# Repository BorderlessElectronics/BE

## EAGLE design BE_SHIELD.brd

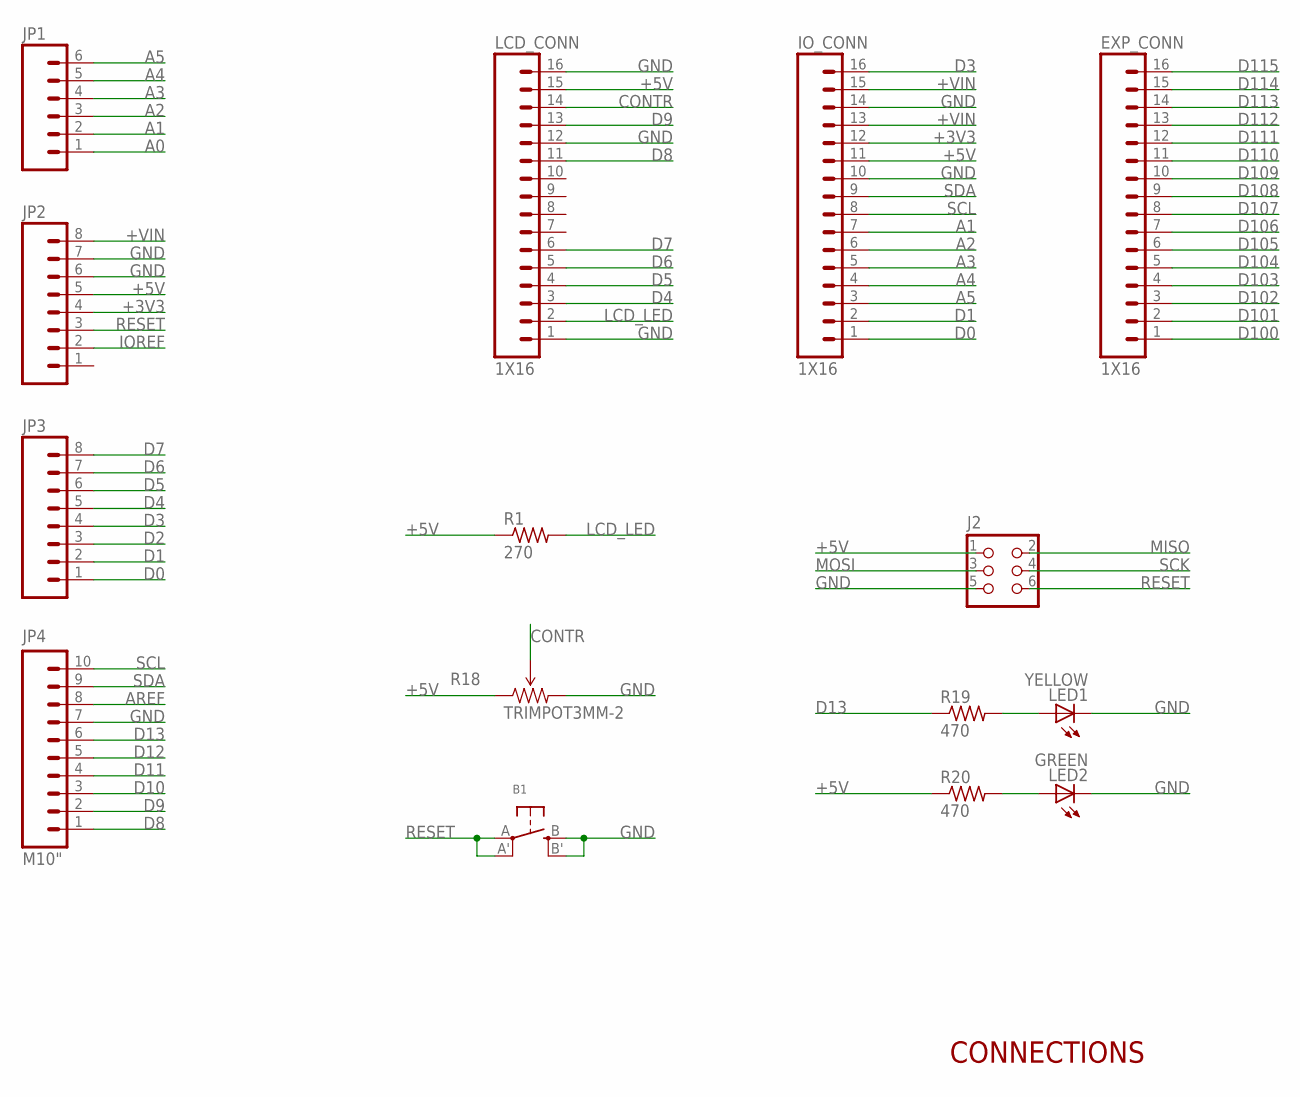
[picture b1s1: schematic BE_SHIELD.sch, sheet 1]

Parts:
B1: SWITCH_TACT_SMT; EVQ-Q2
EXP_CONN: 1X16; 1X16_SMD
IO_CONN: 1X16; 1X16_SMD
J2: CON_HEADER_2X03-SMD; M2X3_SMD
JP1: M06SIP; 1X06
JP2, JP3: M081X08; 1X08
JP4: M10"; 1X10
LCD_CONN: 1X16; 1X16_SMD
LED1: YELLOW; CHIP-LED0805
LED2: GREEN; CHIP-LED0805
R1: 270; R0603
R18: TRIMPOT3MM-2; TRIMPOT-3MM-2
R19, R20: 470; R0603

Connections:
+3V3: IO_CONN.12, JP2.4; also elsewhere on the board
+5V: IO_CONN.11, J2.1, JP2.5, LCD_CONN.15, R1.1, R18.1 (CCW), R20.1; also elsewhere on the board
+VIN: IO_CONN.13, IO_CONN.15, JP2.8; also elsewhere on the board
A0: JP1.1; also elsewhere on the board
A1: IO_CONN.7, JP1.2; also elsewhere on the board
A2: IO_CONN.6, JP1.3; also elsewhere on the board
A3: IO_CONN.5, JP1.4; also elsewhere on the board
A4: IO_CONN.4, JP1.5; also elsewhere on the board
A5: IO_CONN.3, JP1.6; also elsewhere on the board
AREF: JP4.8
CONTR: LCD_CONN.14, R18.2 (WIPER); also elsewhere on the board
D0: IO_CONN.1, JP3.1; also elsewhere on the board
D1: IO_CONN.2, JP3.2; also elsewhere on the board
D2: JP3.3; also elsewhere on the board
D3: IO_CONN.16, JP3.4; also elsewhere on the board
D4: JP3.5, LCD_CONN.3; also elsewhere on the board
D5: JP3.6, LCD_CONN.4; also elsewhere on the board
D6: JP3.7, LCD_CONN.5; also elsewhere on the board
D7: JP3.8, LCD_CONN.6; also elsewhere on the board
D8: JP4.1, LCD_CONN.11; also elsewhere on the board
D9: JP4.2, LCD_CONN.13; also elsewhere on the board
D10: JP4.3; also elsewhere on the board
D11: JP4.4
D12: JP4.5
D13: JP4.6, R19.1
GND: B1.B (S), B1.B' (S1), IO_CONN.10, IO_CONN.14, J2.5, JP2.6, JP2.7, JP4.7, LCD_CONN.1, LCD_CONN.12, LCD_CONN.16, LED1.C, LED2.C, R18.3 (CW); also elsewhere on the board
IOREF: JP2.2
LCD_LED: LCD_CONN.2, R1.2; also elsewhere on the board
MISO: J2.2; also elsewhere on the board
MOSI: J2.3; also elsewhere on the board
unnamed: LED2.A, R20.2
unnamed: LED1.A, R19.2
RESET: B1.A, B1.A' (P1), J2.6, JP2.3; also elsewhere on the board
SCK: J2.4; also elsewhere on the board
SCL: IO_CONN.8, JP4.10; also elsewhere on the board
SDA: IO_CONN.9, JP4.9; also elsewhere on the board

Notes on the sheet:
CONNECTIONS

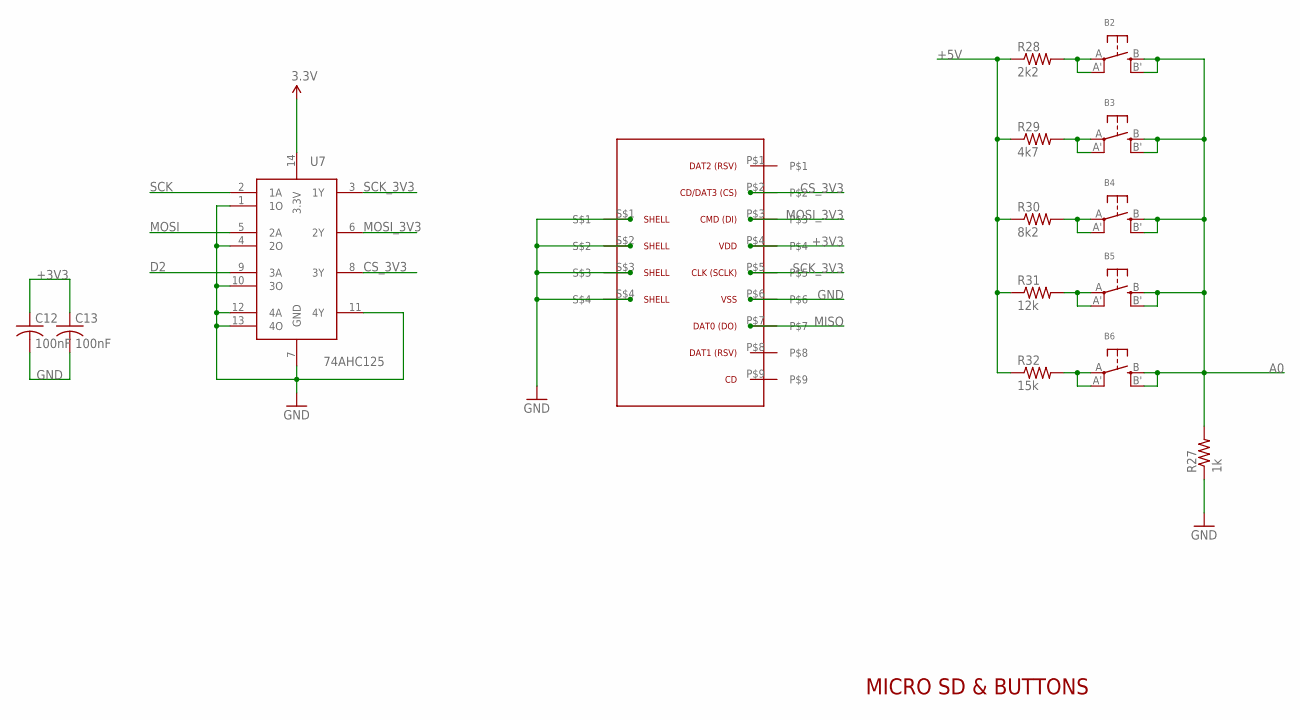
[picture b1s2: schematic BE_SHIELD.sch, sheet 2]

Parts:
B2, B3, B4, B5, B6: SWITCH_TACT_SMT; EVQ-Q2
C12, C13: 100nF; C0603K
R27: 1k; R0603
R28: 2k2; R0603
R29: 4k7; R0603
R30: 8k2; R0603
R31: 12k; R0603
R32: 15k; R0603
U7: 74AHC125; SO014
U$3: TFWF6-EBS1-1102

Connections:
+3V3: C12.1, C13.1, U7.14 (3.3V), U$3.P$4; also elsewhere on the board
+5V: R28.1, R29.1, R30.1, R31.1, R32.1; also elsewhere on the board
A0: B2.B (S), B2.B' (S1), B3.B (S), B3.B' (S1), B4.B (S), B4.B' (S1), B5.B (S), B5.B' (S1), B6.B (S), B6.B' (S1), R27.2; also elsewhere on the board
CS_3V3: U7.8 (3Y), U$3.P$2
D2: U7.9 (3A); also elsewhere on the board
GND: C12.2, C13.2, R27.1, U7.1 (1O), U7.4 (2O), U7.7 (GND), U7.10 (3O), U7.11 (4Y), U7.12 (4A), U7.13 (4O), U$3.P$6, U$3.S$1, U$3.S$2, U$3.S$3, U$3.S$4; also elsewhere on the board
MISO: U$3.P$7; also elsewhere on the board
MOSI: U7.5 (2A); also elsewhere on the board
MOSI_3V3: U7.6 (2Y), U$3.P$3
unnamed: B2.A, B2.A' (P1), R28.2
unnamed: B3.A, B3.A' (P1), R29.2
unnamed: B4.A, B4.A' (P1), R30.2
unnamed: B5.A, B5.A' (P1), R31.2
unnamed: B6.A, B6.A' (P1), R32.2
SCK: U7.2 (1A); also elsewhere on the board
SCK_3V3: U7.3 (1Y), U$3.P$5

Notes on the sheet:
MICRO SD & BUTTONS

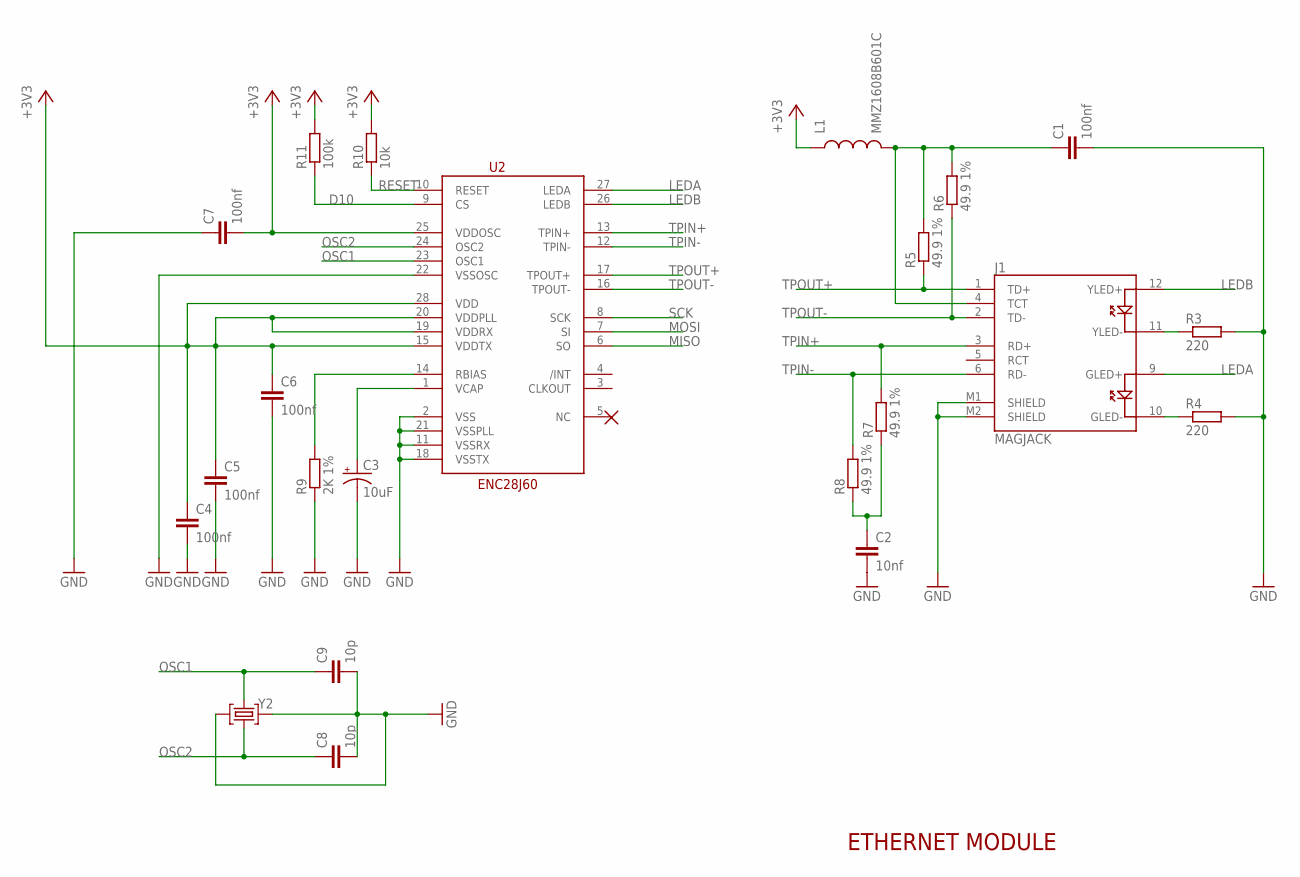
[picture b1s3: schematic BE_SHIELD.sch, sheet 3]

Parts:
C1, C4, C5, C6, C7: 100nf; 0603-CAP
C2: 10nf; 0603-CAP
C3: 10uF; EIA3216
C8, C9: 10p; 0603-CAP
J1: MAGJACK
L1: MMZ1608B601C; 0603
R3, R4: 220; R0603
R5, R6, R7, R8: 49.9 1%; R0603
R9: 2K 1%; R0603
R10: 10k; R0603
R11: 100k; R0603
U2: ENC28j60; SSOP28DB
Y2: 25MHz; CRYSTAL-3.2-2.5

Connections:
+3V3: C4.1, C5.1, C6.1, C7.2, L1.1, R10.2, R11.2, U2.15 (VDDTX), U2.19 (VDDRX), U2.20 (VDDPLL), U2.25 (VDDOSC), U2.28 (VDD); also elsewhere on the board
D10: R11.1, U2.9 (CS); also elsewhere on the board
GND: C1.2, C2.2, C3.C (-), C4.2, C5.2, C6.2, C7.1, C8.2, C9.2, J1.M1 (SHIELD), J1.M2 (SHIELD), R3.2, R4.2, R9.1, U2.2 (VSS), U2.11 (VSSRX), U2.18 (VSSTX), U2.21 (VSSPLL), U2.22 (VSSOSC), Y2.2 (GND), Y2.4 (GND); also elsewhere on the board
LEDA: J1.9 (GLED+), U2.27 (LEDA)
LEDB: J1.12 (YLED+), U2.26 (LEDB)
MISO: U2.6 (SO); also elsewhere on the board
MOSI: U2.7 (SI); also elsewhere on the board
unnamed: C2.1, R7.1, R8.1
unnamed: J1.11 (YLED-), R3.1
unnamed: R9.2, U2.14 (RBIAS)
unnamed: J1.10 (GLED-), R4.1
unnamed: C3.A (+), U2.1 (VCAP)
unnamed: C1.1, J1.4 (TCT), L1.2, R5.2, R6.2
OSC1: C9.1, U2.23 (OSC1), Y2.3 (C2)
OSC2: C8.1, U2.24 (OSC2), Y2.1 (C1)
RESET: R10.1, U2.10 (RESET); also elsewhere on the board
SCK: U2.8 (SCK); also elsewhere on the board
TPIN+: J1.3 (RD+), R7.2, U2.13 (TPIN+)
TPIN-: J1.6 (RD-), R8.2, U2.12 (TPIN-)
TPOUT+: J1.1 (TD+), R5.1, U2.17 (TPOUT+)
TPOUT-: J1.2 (TD-), R6.1, U2.16 (TPOUT-)

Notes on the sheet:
ETHERNET MODULE

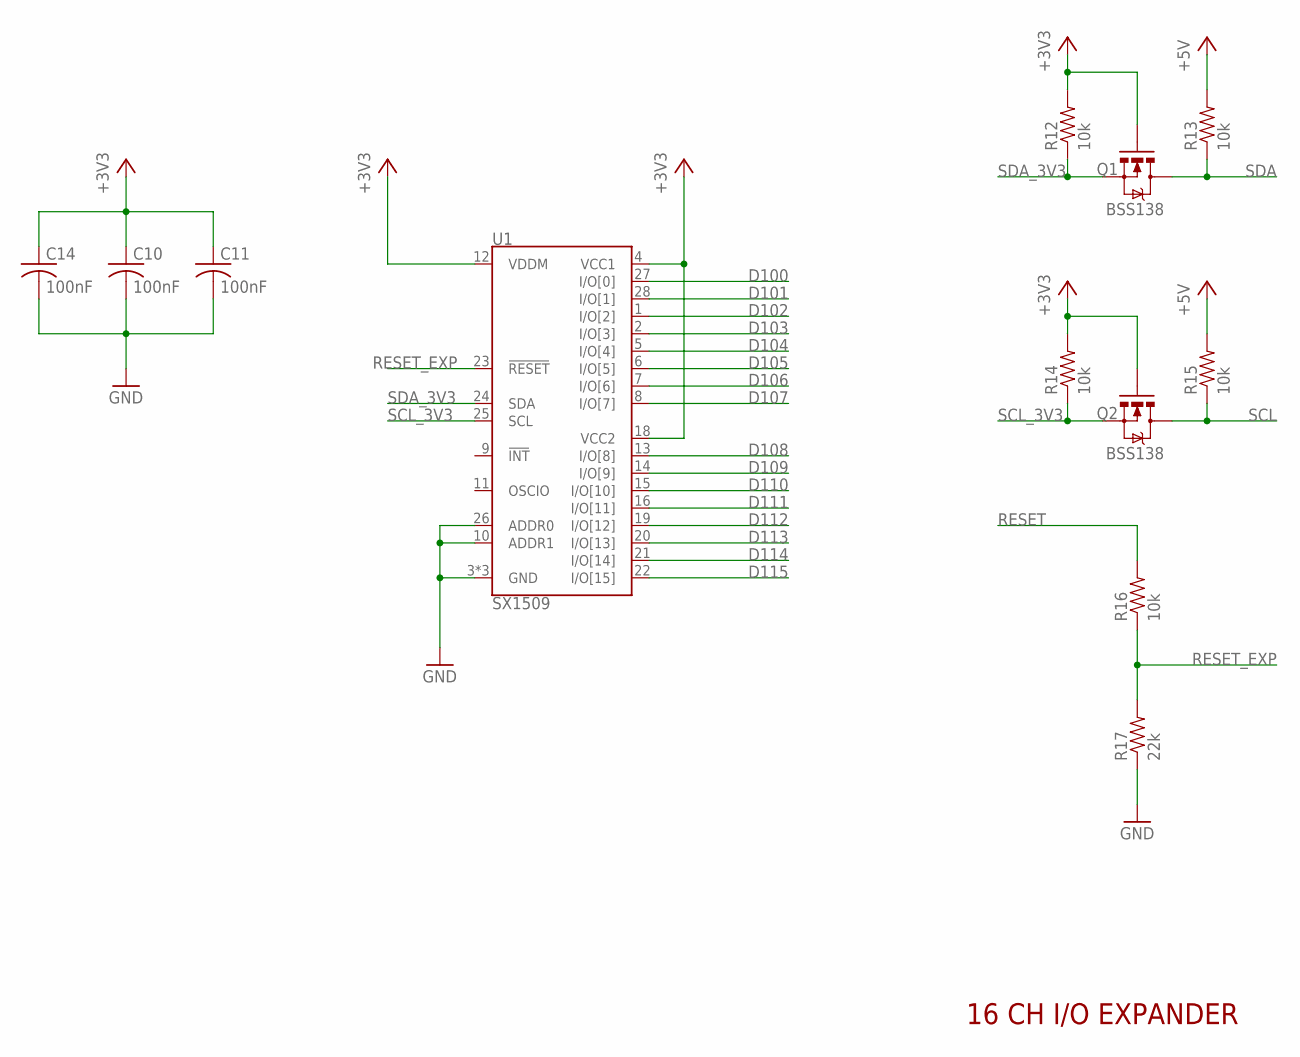
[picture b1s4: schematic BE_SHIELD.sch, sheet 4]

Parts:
C10, C11, C14: 100nF; C0603K
Q1, Q2: BSS138; SOT23-3
R12, R13, R14, R15, R16: 10k; 0603-RES
R17: 22k; 0603-RES
U1: SX1509; QFN-28

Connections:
+3V3: C10.1, C11.1, C14.1, Q1.1 (G), Q2.1 (G), R12.2, R14.2, U1.4 (VCC1), U1.12 (VDDM), U1.18 (VCC2); also elsewhere on the board
+5V: R13.2, R15.2; also elsewhere on the board
D100: U1.27 (I/O[0]); also elsewhere on the board
D101: U1.28 (I/O[1]); also elsewhere on the board
D102: U1.1 (I/O[2]); also elsewhere on the board
D103: U1.2 (I/O[3]); also elsewhere on the board
D104: U1.5 (I/O[4]); also elsewhere on the board
D105: U1.6 (I/O[5]); also elsewhere on the board
D106: U1.7 (I/O[6]); also elsewhere on the board
D107: U1.8 (I/O[7]); also elsewhere on the board
D108: U1.13 (I/O[8]); also elsewhere on the board
D109: U1.14 (I/O[9]); also elsewhere on the board
D110: U1.15 (I/O[10]); also elsewhere on the board
D111: U1.16 (I/O[11]); also elsewhere on the board
D112: U1.19 (I/O[12]); also elsewhere on the board
D113: U1.20 (I/O[13]); also elsewhere on the board
D114: U1.21 (I/O[14]); also elsewhere on the board
D115: U1.22 (I/O[15]); also elsewhere on the board
GND: C10.2, C11.2, C14.2, R17.1, U1.3 (GND), U1.10 (ADDR1), U1.17 (GND), U1.26 (ADDR0), U1.29 (GND); also elsewhere on the board
RESET: R16.2; also elsewhere on the board
RESET_EXP: R16.1, R17.2, U1.23 (!RESET)
SCL: Q2.3 (D), R15.1; also elsewhere on the board
SCL_3V3: Q2.2 (S), R14.1, U1.25 (SCL)
SDA: Q1.3 (D), R13.1; also elsewhere on the board
SDA_3V3: Q1.2 (S), R12.1, U1.24 (SDA)

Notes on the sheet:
16 CH I/O EXPANDER

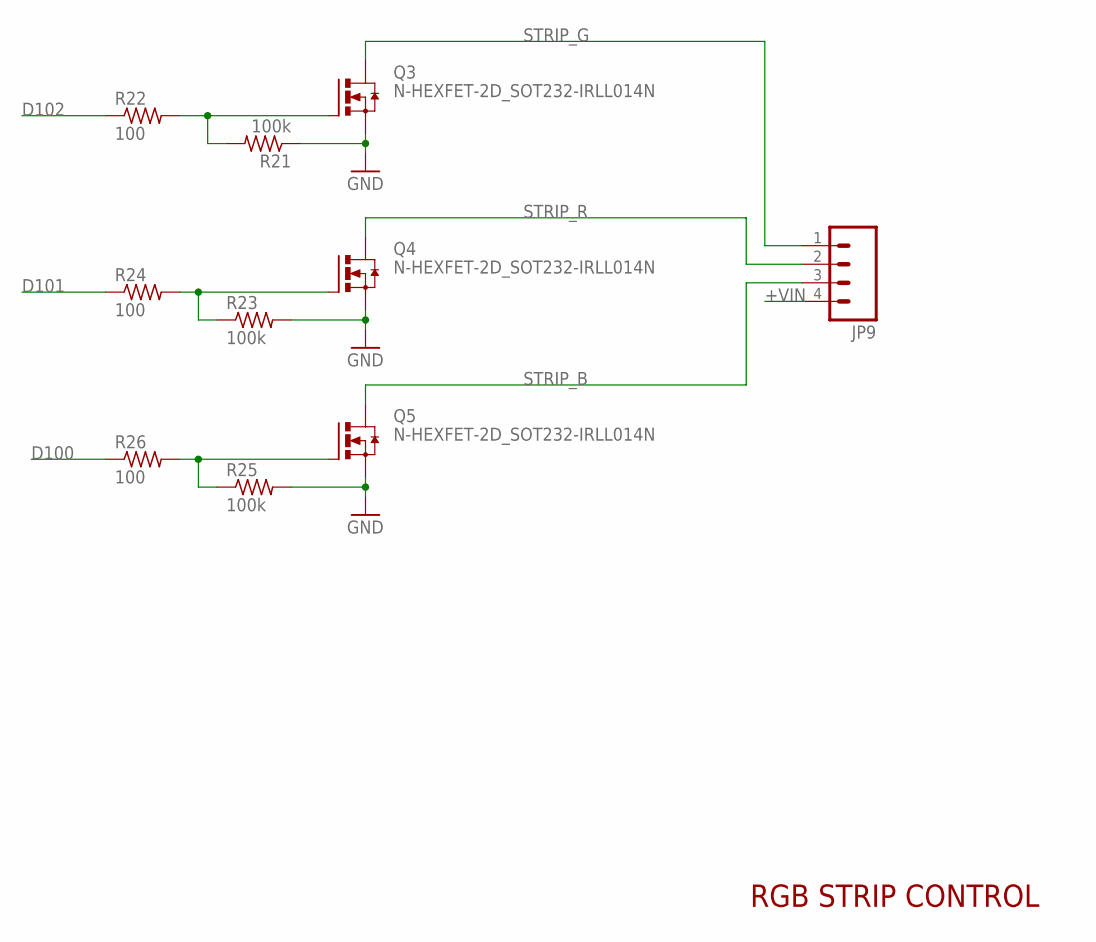
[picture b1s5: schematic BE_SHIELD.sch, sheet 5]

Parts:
JP9: M04SMD; 1X04-SMD
Q3, Q4, Q5: N-HEXFET-2D_SOT232-IRLL014N; SOT223
R21, R23, R25: 100k; R0603
R22, R24, R26: 100; R0603

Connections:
+VIN: JP9.4; also elsewhere on the board
D100: R26.1; also elsewhere on the board
D101: R24.1; also elsewhere on the board
D102: R22.1; also elsewhere on the board
GND: Q3.3 (S), Q4.3 (S), Q5.3 (S), R21.1, R23.2, R25.2; also elsewhere on the board
unnamed: Q5.1 (G), R25.1, R26.2
unnamed: Q3.1 (G), R21.2, R22.2
unnamed: Q4.1 (G), R23.1, R24.2
STRIP_B: JP9.3, Q5.2 (D), Q5.4 (D)
STRIP_G: JP9.1, Q3.2 (D), Q3.4 (D)
STRIP_R: JP9.2, Q4.2 (D), Q4.4 (D)

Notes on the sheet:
RGB STRIP CONTROL

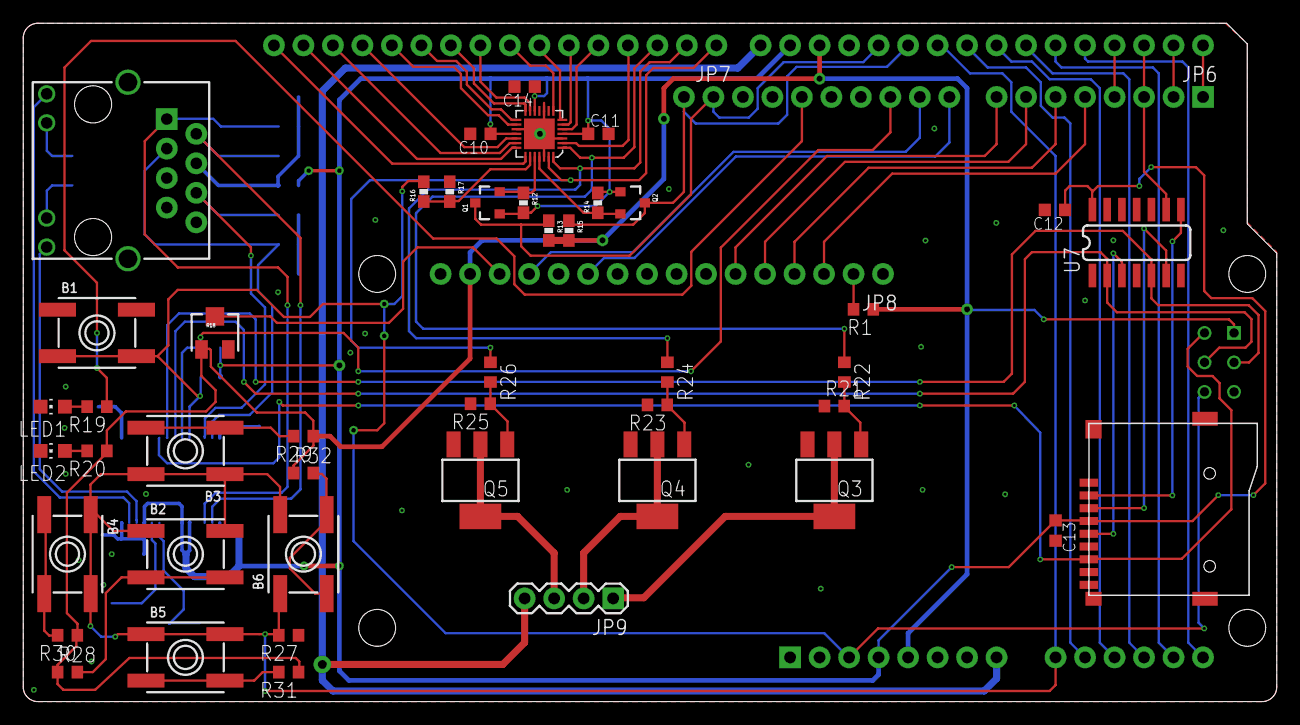
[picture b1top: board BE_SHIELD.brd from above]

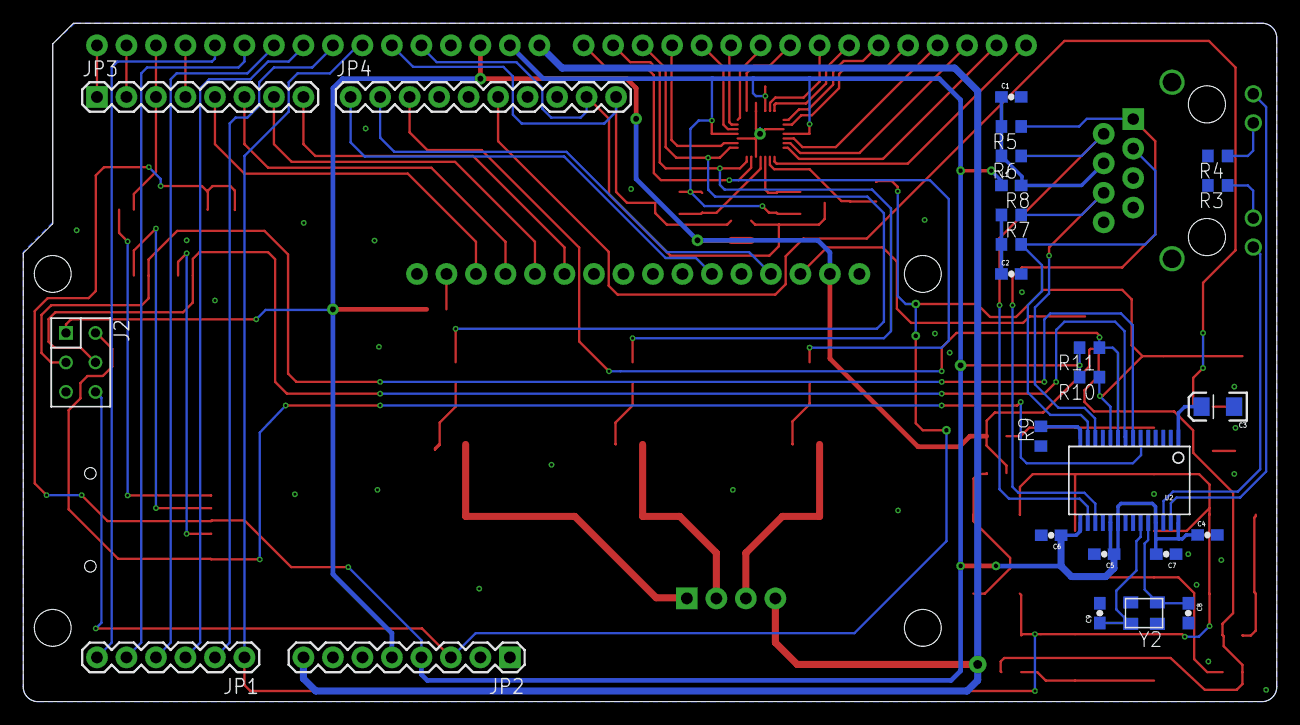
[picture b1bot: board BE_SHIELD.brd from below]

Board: 2 copper layers, 108.0 x 58.4 mm, 74 parts (26 on the bottom side), 79 nets.

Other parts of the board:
JP6, JP7, JP8: M161X16_NO_SILK; 1X16_NO_SILK

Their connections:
+3V3: JP6.15; also elsewhere on the board
+5V: JP6.14, JP8.15; also elsewhere on the board
+VIN: JP6.16; also elsewhere on the board
A0: JP6.10; also elsewhere on the board
A1: JP6.9; also elsewhere on the board
A2: JP6.8; also elsewhere on the board
A3: JP6.7; also elsewhere on the board
A4: JP6.6; also elsewhere on the board
A5: JP6.5; also elsewhere on the board
CONTR: JP8.14; also elsewhere on the board
D0: JP6.1; also elsewhere on the board
D1: JP6.2; also elsewhere on the board
D2: JP6.3; also elsewhere on the board
D3: JP6.4; also elsewhere on the board
D4: JP8.3; also elsewhere on the board
D5: JP8.4; also elsewhere on the board
D6: JP8.5; also elsewhere on the board
D7: JP8.6; also elsewhere on the board
D8: JP8.11; also elsewhere on the board
D9: JP8.13; also elsewhere on the board
D100: JP7.1; also elsewhere on the board
D101: JP7.2; also elsewhere on the board
D102: JP7.3; also elsewhere on the board
D103: JP7.4; also elsewhere on the board
D104: JP7.5; also elsewhere on the board
D105: JP7.6; also elsewhere on the board
D106: JP7.7; also elsewhere on the board
D107: JP7.8; also elsewhere on the board
D108: JP7.9; also elsewhere on the board
D109: JP7.10; also elsewhere on the board
D110: JP7.11; also elsewhere on the board
D111: JP7.12; also elsewhere on the board
D112: JP7.13; also elsewhere on the board
D113: JP7.14; also elsewhere on the board
D114: JP7.15; also elsewhere on the board
D115: JP7.16; also elsewhere on the board
GND: JP6.13, JP8.1, JP8.12, JP8.16; also elsewhere on the board
LCD_LED: JP8.2; also elsewhere on the board
SCL: JP6.11; also elsewhere on the board
SDA: JP6.12; also elsewhere on the board

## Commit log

2014-06-01 BRD and SCH files for Eagle
    BRD and SCH files

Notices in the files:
parts and their libraries:
SparkFun-Connectors: Licensing: CC v3.0 Share-Alike You are welcome to use this library for commercial purposes.
microbuilder: This work is placed in the public domain, and may be freely used for commercial and non-commercial work with the following conditions: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
